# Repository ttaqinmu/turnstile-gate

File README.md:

# Ticket turnstile gate wiring concept — one 90° swing leaf

Purchasing document: [Electrical bill of materials and component plan](./BOM-elektrikal.md).

KiCad schematic: [open the KiCad project](./kicad/turnstile-gate.kicad_pro) or [open the schematic directly](./kicad/turnstile-gate.kicad_sch). Read the [KiCad guide](./kicad/README.md) before using symbol pin numbers.

Control PCB: [layout](./kicad/control-board/control-board.kicad_pcb), [preview](./kicad/control-board/control-board-preview.svg), and [terminal guide](./kicad/control-board/README.md). This board carries 5 V/3.3 V signals; the 24 V power circuit and motor remain in the electrical panel.

Blender hardware model: [hardware.blend](./hardware.blend) and its [model and animation guide](./blender/README.md).

This is a **concept-level design for a full-size gate** using an ESP32-DevKitC V4 (ESP32-WROOM module), a 3.3 V UART QR scanner, a 24 V DC gearmotor, and an IR through beam pair. Select the motor and mechanism based on leaf weight, arm length, opening time, and motor stall current. The design is not a fabrication drawing or a safety certification. The Blender model currently shows a reflective IR module inside the upper beam; that placement does not yet match the through beam electrical design. Resolve the sensor choice and update both designs before fabrication.

## Main components

| Ref. | Component | Notes |
|---|---|---|
| PS1 | 24 V DC power supply | Size its current capacity for the motor and total load. Have a qualified electrician handle AC wiring and frame grounding. |
| F1 | Motor fuse | Size for the cable, driver, and motor current. |
| F2 | Control fuse | Size for the buck converter and control wiring. |
| S0, K1 | NC emergency stop + 24 V DC contactor/relay | S0 interrupts the K1 coil; the K1 NO contact disconnects the motor driver's `VIN`. Select DC-rated contacts for the motor current. Fit a flyback diode across the DC coil. Public installations require a safety circuit based on a risk assessment. |
| U1 | 24 V → 5 V buck converter | Powers the ESP32 through its `5V` pin; do not power it from USB at the same time. |
| U2 | ESP32-DevKitC V4 | Use the WROOM version so GPIO16/17 are available. |
| U3 | DFRobot SEN0486 QR scanner | Powered at 3.3 V; UART interface. |
| U4 | 24 V H-bridge driver | Example: Pololu G2 24v30 CS. Continuous and starting current, protection, cooling, and current limits must suit the motor. |
| M1 | 24 V DC gearmotor | The mechanism swings the leaf from 0° to 90°; provide mechanical stops at both ends. |
| B1 | IR through beam transmitter and receiver | The receiver needs a **voltage-free relay contact** that closes only when the path is clear **and the sensor is powered**. This generally means an energised relay when the beam is received, using `COM-NO`; check the chosen sensor's contact diagram. U5 isolates the contact from the ESP32. |
| U5 | PC817 optocoupler + 330 Ω resistor | Draws about 11 mA through B1's relay contact from 5 V and converts the result to a 3.3 V-safe GPIO32 signal. |
| S1, S2 | 0° and 90° limit switches | NC contacts that open at the respective end positions. |

## Electrical connections

| From | To | Purpose |
|---|---|---|
| PS1 `+24V` | F1 → K1 NO contact → U4 `VIN` | Motor power that the emergency stop can disconnect. |
| F2 output `+24V` | S0 NC → K1 coil → PS1 `0V` | Pressing S0 or breaking its cable releases K1. Fit a correctly polarised flyback diode across the coil. |
| PS1 `+24V` | F2 → U1 `IN+` and B1 supply `+` | Control and IR sensor power, subject to the sensor's rating. |
| PS1 `0V` | U4 `GND`; U1 `IN−`; B1 supply `−` | Supply return. Route motor current separately from signal wiring and join them at the distribution point. |
| U1 `5V+`, `5V−` | U2 `5V`, `GND` | ESP32 power. |
| U2 `3V3`, `GND` | U3 `VCC`, `GND` | Power the QR scanner at 3.3 V. |
| U3 `SDA/TX` | U2 `GPIO16` (UART RX) | Scan data. |
| U2 `GPIO17` (UART TX) | U3 `SCL/RX` | Optional scanner commands/configuration. |
| U2 `GPIO25` | U4 `PWM` | Motor speed. |
| U2 `GPIO26` | U4 `DIR` | Opening/closing direction; verify motor polarity during commissioning. |
| U2 `GND` | U4 `GND` | Driver signal reference. |
| U4 `OUTA`, `OUTB` | M1 terminals A, B | Two motor leads. |
| U4 `FLT` | U2 `GPIO27` + 10 kΩ pull-up to `3V3` | Active-low driver fault. |
| U1 `5V+` | 330 Ω / 0.5 W resistor → U5 LED anode; U5 LED cathode → B1 `COM`; B1 `NO` → U1 `5V−` | About (5 − 1.2)/330 = 11.5 mA through the relay contact when the path is clear. This meets the example Omron E3JK sensor's 5 V / 10 mA minimum load. Check U5 LED polarity. |
| U5 transistor collector, emitter | U2 `GPIO32` + 10 kΩ pull-up to `3V3`, U2 `GND` | `LOW` = clear path; `HIGH` = blocked path, unpowered sensor, or broken cable. Verify all three cases. |
| S1 `COM`, `NC` | U2 `GND`, `GPIO33` + 10 kΩ pull-up to `3V3` | `HIGH` = gate reaches 0° or the cable is broken. |
| S2 `COM`, `NC` | U2 `GND`, `GPIO34` + **external** 10 kΩ pull-up to `3V3` | `HIGH` = gate reaches 90° or the cable is broken. GPIO34 has no internal pull-up. |

Add an electrolytic capacitor close to the driver's `VIN`/`GND` as specified by its documentation (at least several hundred µF, with a voltage rating above 24 V). Do not power the ESP32 from the motor driver's `3V3 (out)` pin. Mount U5 on a protected, rigid PCB or perfboard inside the panel; do not use a breadboard for permanent installation.

## Control sequence

1. After a valid QR scan, check that S0 is inactive, the limit switches are consistent, the driver has no fault, and the IR path is clear.
2. Drive the motor open with a gentle PWM ramp until S2 indicates 90°. Stop on a timeout or fault.
3. Wait for a person to pass: the IR beam must first be interrupted and then become clear. After a safe delay, begin closing only if additional safety sensing confirms that the leaf's swing area is clear.
4. If the IR path is blocked while closing, **stop and reopen**. Stop at S1 (0°).
5. On a fault, loss of sensor power, or failure to reach a limit within the allowed time, disable the drive and request operator inspection. Never close solely on a timer.

Place the IR beam across the walking path, outside the leaf's swing area. A single beam can miss a child, luggage, or a person standing elsewhere. A public gate requires mechanical risk assessment, additional safety sensors, force/speed limits, and a manual release for power failures.

## Component references

- [Espressif ESP32-DevKitC V4: pinout and power rules](https://docs.espressif.com/projects/esp-idf/en/v5.3.1/esp32/hw-reference/esp32/get-started-devkitc.html)
- [DFRobot SEN0486: specifications, UART, and pinout](https://wiki.dfrobot.com/sen0486/)
- [Pololu G2 24v30 CS: pinout, electrical limits, and supply capacitor](https://www.pololu.com/product/5692)

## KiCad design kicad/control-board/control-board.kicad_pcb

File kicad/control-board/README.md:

# Turnstile gate control PCB — rev A

[Open the KiCad layout](./control-board.kicad_pcb) · [Preview](./control-board-preview.svg) · [DRC report](./control-board-drc.txt)

This **115 × 95 mm**, two-layer PCB is a carrier for the **ESP32-DevKitC V4 with an ESP32-WROOM module**. It holds two 19-pin sockets, a PC817, a 330 Ω/0.5 W resistor, four 10 kΩ pull-ups, signal terminals, and four M3 mounting holes. PCB traces are 0.30 mm wide. An external buck converter supplies 5 V.

**The PCB carries only 5 V, 3.3 V, and signals.** The 24 V supply, fuses, emergency stop, power-cut relay, motor driver, power capacitor, motor, and IR sensor supply are installed in the panel according to the [system schematic](../turnstile-gate.kicad_sch). The PCB's IR terminal carries only the sensor's relay contact. Motor current does not flow through this PCB.

## PCB terminals

Read terminal pin numbers from the pin 1 marking on each footprint and the PCB top view. Do not infer wire order from the SVG preview alone; check pad numbers in KiCad before assembly.

| Terminal | Pin 1 | Pin 2 | Pin 3 | Pin 4 |
|---|---|---|---|---|
| J1 — external buck input | +5 V | GND | — | — |
| J2 — SEN0486 QR scanner | 3V3 | GND | scanner `SDA/TX` → GPIO16 | scanner `SCL/RX` ← GPIO17 |
| J3 — Pololu driver logic | GND | PWM/GPIO25 | DIR/GPIO26 | FLT/GPIO27 |
| J4 — IR relay | sensor `COM` | sensor `NO` | — | — |
| J5 — 0° NC limit | COM/GND | NC/GPIO33 | — | — |
| J6 — 90° NC limit | COM/GND | NC/GPIO34 | — | — |

The Pololu G2 24v30 CS driver's `SLP` connection is not required here because the driver module already pulls that pin up and enables it by default. Wire power `VIN`, power `GND`, `OUTA`, and `OUTB` directly at the driver/panel using conductors rated for the actual current.

## ESP32 and board components

- J7 = ESP32 `J2` socket per the [Espressif pin table](https://docs.espressif.com/projects/esp-dev-kits/en/latest/esp32/esp32-devkitc/user_guide.html#header-block). Pin 1 `3V3`, 5 `GPIO34`, 7 `GPIO32`, 8 `GPIO33`, 9 `GPIO25`, 10 `GPIO26`, 11 `GPIO27`, 14 `GND`, 19 `5V`.
- J8 = ESP32 `J3` socket. Pins 1 and 7 are `GND`; pin 11 is `GPIO17`, and pin 12 is `GPIO16`.
- J7 and J8 have **25.40 mm** between rows. Check this against the [official DevKitC V4 dimensions](https://dl.espressif.com/dl/schematics/esp32_devkitc_v4_dimensions.pdf) and the physical module before fabrication. The WROVER version is unsuitable because it uses GPIO16/17 internally.
- Physical U5 PC817 pins: 1 anode, 2 cathode, **3 emitter/GND, 4 collector/GPIO32**. R1 is 330 Ω/0.5 W in series with the U5 LED. R2–R5 are 10 kΩ pull-ups to 3V3 for IR, HOME, OPEN, and FLT.
- J1 powers the ESP32 `5V` pin. Do not also power it over USB while J1 is live; [Espressif specifies one power source at a time](https://docs.espressif.com/projects/esp-dev-kits/en/latest/esp32/esp32-devkitc/user_guide.html#power-supply-options).

## Checks and design limits

KiCad 10.0.7 DRC: **0 violations, 0 unconnected items**. This confirms that the layout rules and all defined nets are connected. This PCB does not yet have its own PCB schematic synchronised through *Update PCB from Schematic*. The [system schematic](../turnstile-gate.kicad_sch) also depicts panel components and uses logical module pin numbers. Cross-check all terminals against the table above before production.

Before ordering the PCB, print it at 1:1 scale and check the physical ESP32 and terminal blocks for size and orientation. Check USB and antenna clearance, socket height, component spacing, cable connectors, and M3 holes. The preview and DRC do not replace an assembly test. A public gate needs mechanical/electrical safety assessment and additional safety sensors; this control board is not a certified safety device.

## Regenerating the board

`prepare_footprints.py` copies stock KiCad footprints into the project. Run `generate_board.py`, then `route_board.py`, using Python with KiCad 10's `pcbnew` module. The `.kicad_pcb` file embeds its footprints and can be opened without the scripts; footprint copies are included so the generator can be rerun.

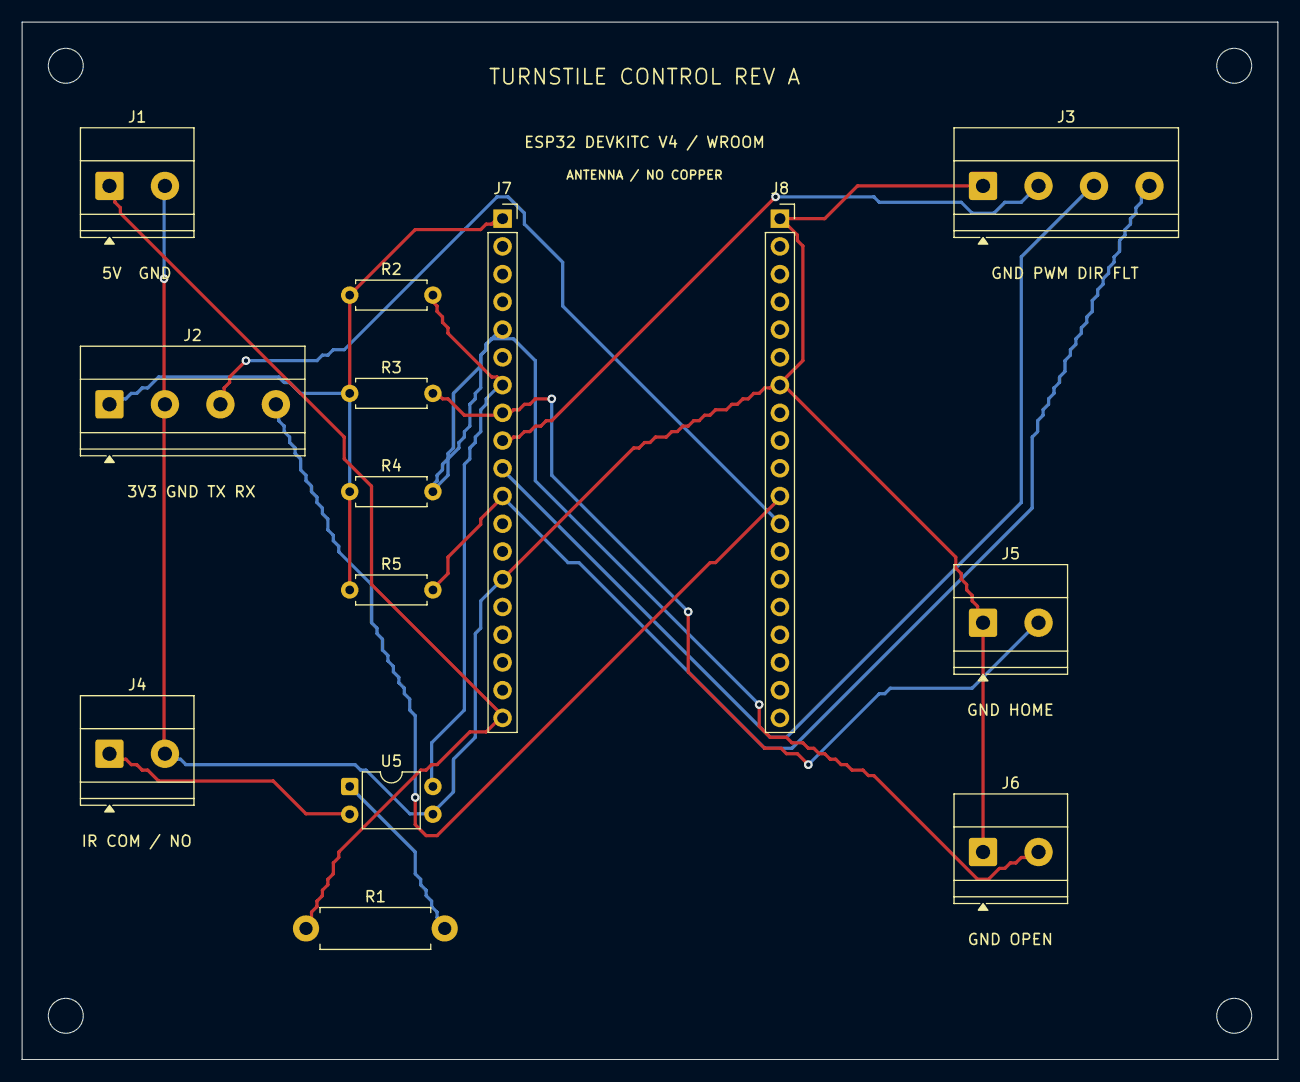
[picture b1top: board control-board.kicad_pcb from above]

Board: 2 copper layers, 115.0 x 95.0 mm, 18 parts (0 on the bottom side), 13 nets.

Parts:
H1, H2, H3, H4: M3; MountingHole_3.2mm_M3
J1: 5V BUCK; TerminalBlock_Phoenix_MKDS-1,5-2-5.08_1x02_P5.08mm_Horizont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
J2: QR UART; TerminalBlock_Phoenix_MKDS-1,5-4-5.08_1x04_P5.08mm_Horizont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
J3: MOTOR DRIVER LOGIC; TerminalBlock_Phoenix_MKDS-1,5-4-5.08_1x04_P5.08mm_Horizont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
J4: IR RELAY COM NO; TerminalBlock_Phoenix_MKDS-1,5-2-5.08_1x02_P5.08mm_Horizont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
J5: LIMIT HOME NC; TerminalBlock_Phoenix_MKDS-1,5-2-5.08_1x02_P5.08mm_Horizont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
J6: LIMIT OPEN NC; TerminalBlock_Phoenix_MKDS-1,5-2-5.08_1x02_P5.08mm_Horizont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
J7: ESP32 J2; PinSocket_1x19_P2.54mm_Vertical
J8: ESP32 J3; PinSocket_1x19_P2.54mm_Vertical
R1: 330R 0.5W; R_Axial_DIN0411_L9.9mm_D3.6mm_P12.70mm_Horizontal
R2: 10k IR; R_Axial_DIN0207_L6.3mm_D2.5mm_P7.62mm_Horizontal
R3: 10k HOME; R_Axial_DIN0207_L6.3mm_D2.5mm_P7.62mm_Horizontal
R4: 10k OPEN; R_Axial_DIN0207_L6.3mm_D2.5mm_P7.62mm_Horizontal
R5: 10k FLT; R_Axial_DIN0207_L6.3mm_D2.5mm_P7.62mm_Horizontal
U5: PC817; DIP-4_W7.62mm

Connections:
+3V3: J2.1, J7.1, R2.1, R3.1, R4.1, R5.1
+5V: J1.1, J7.19, R1.1
DIR26: J3.3, J7.10
FLT27: J3.4, J7.11, R5.2
GND: J1.2, J2.2, J3.1, J4.2, J5.1, J6.1, J7.14, J8.1, J8.7, U5.3
HOME33: J5.2, J7.8, R3.2
IR32: J7.7, R2.2, U5.4
IR_COM: J4.1, U5.2
OPEN34: J6.2, J7.5, R4.2
OPTO_ANODE: R1.2, U5.1
PWM25: J3.2, J7.9
QR_RX: J2.4, J8.11
QR_TX: J2.3, J8.12
